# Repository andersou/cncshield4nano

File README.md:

# CNCShield4Nano

Shield para dar suporte CNC ao Arduino Nano com 3-eixos.

## Características
* Possibilidade de prototipação (basicamente 1 camada)
* Aproveitamento de espaço
* Conector separado para alimentação externa do motor

## Board 

![Desenho da placa][placa-img]

## Esquemático

![Esquematico][sch-img]

[placa-img]: img/Board.png
[sch-img]: img/Schematic.png

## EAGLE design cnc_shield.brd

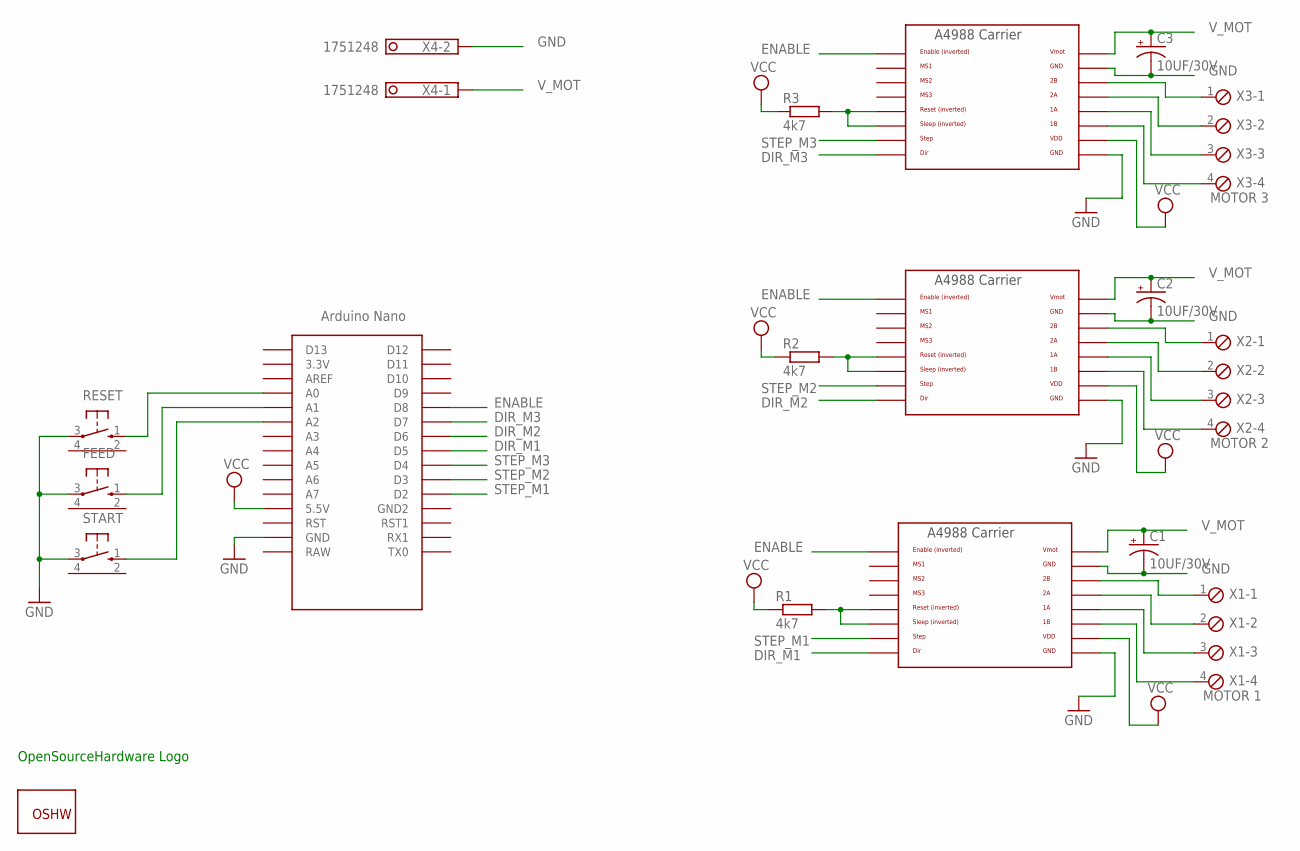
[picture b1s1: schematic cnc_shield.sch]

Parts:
C1, C2, C3: 10UF/30V; E2,5-6
FEED: 10-XX-RPAD; B3F-10XX-RPAD
GOLD_ORB_SM1: OSHWLOGO_GOLD_ORB_SM; OSHW2
R1, R2, R3: 4k7; 0204/5
RESET: 10-XX-RPAD; B3F-10XX-RPAD
START: 10-XX-RPAD; B3F-10XX-RPAD
U$1: NANO
U$2, U$3, U$4: A4988BREAKOUT
X1: MOTOR 1; 4POL254
X2: MOTOR 2; 4POL254
X3: MOTOR 3; 4POL254
X4: 1751248

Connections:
DIR_M1: U$1.D5, U$4.DIR
DIR_M2: U$1.D6, U$2.DIR
DIR_M3: U$1.D7, U$3.DIR
ENABLE: U$1.D8, U$2.EN, U$3.EN, U$4.EN
GND: C1.-, C2.-, C3.-, FEED.3, RESET.3, START.3, U$1.GND, U$2.GND, U$2.GND@0 (GND), U$3.GND, U$3.GND@0 (GND), U$4.GND, U$4.GND@0 (GND), X4.2
unnamed: U$2.2B, X2.1
unnamed: R1.2, U$4.RST, U$4.SLP (SLEEP)
unnamed: U$4.2B, X1.1
unnamed: U$4.2A, X1.2
unnamed: U$4.1A, X1.3
unnamed: U$2.2A, X2.2
unnamed: U$4.1B, X1.4
unnamed: U$2.1A, X2.3
unnamed: U$2.1B, X2.4
unnamed: R2.2, U$2.RST, U$2.SLP (SLEEP)
unnamed: U$3.2B, X3.1
unnamed: U$3.2A, X3.2
unnamed: U$3.1A, X3.3
unnamed: U$3.1B, X3.4
unnamed: R3.2, U$3.RST, U$3.SLP (SLEEP)
unnamed: RESET.1 (S), U$1.A0
unnamed: FEED.1 (S), U$1.A1
unnamed: START.1 (S), U$1.A2
STEP_M1: U$1.D2, U$4.STEP
STEP_M2: U$1.D3, U$2.STEP
STEP_M3: U$1.D4, U$3.STEP
VCC: R1.1, R2.1, R3.1, U$1.5V (5.5V), U$2.VDD, U$3.VDD, U$4.VDD
V_MOT: C1.+, C2.+, C3.+, U$2.VMOT, U$3.VMOT, U$4.VMOT, X4.1

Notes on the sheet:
OpenSourceHardware Logo

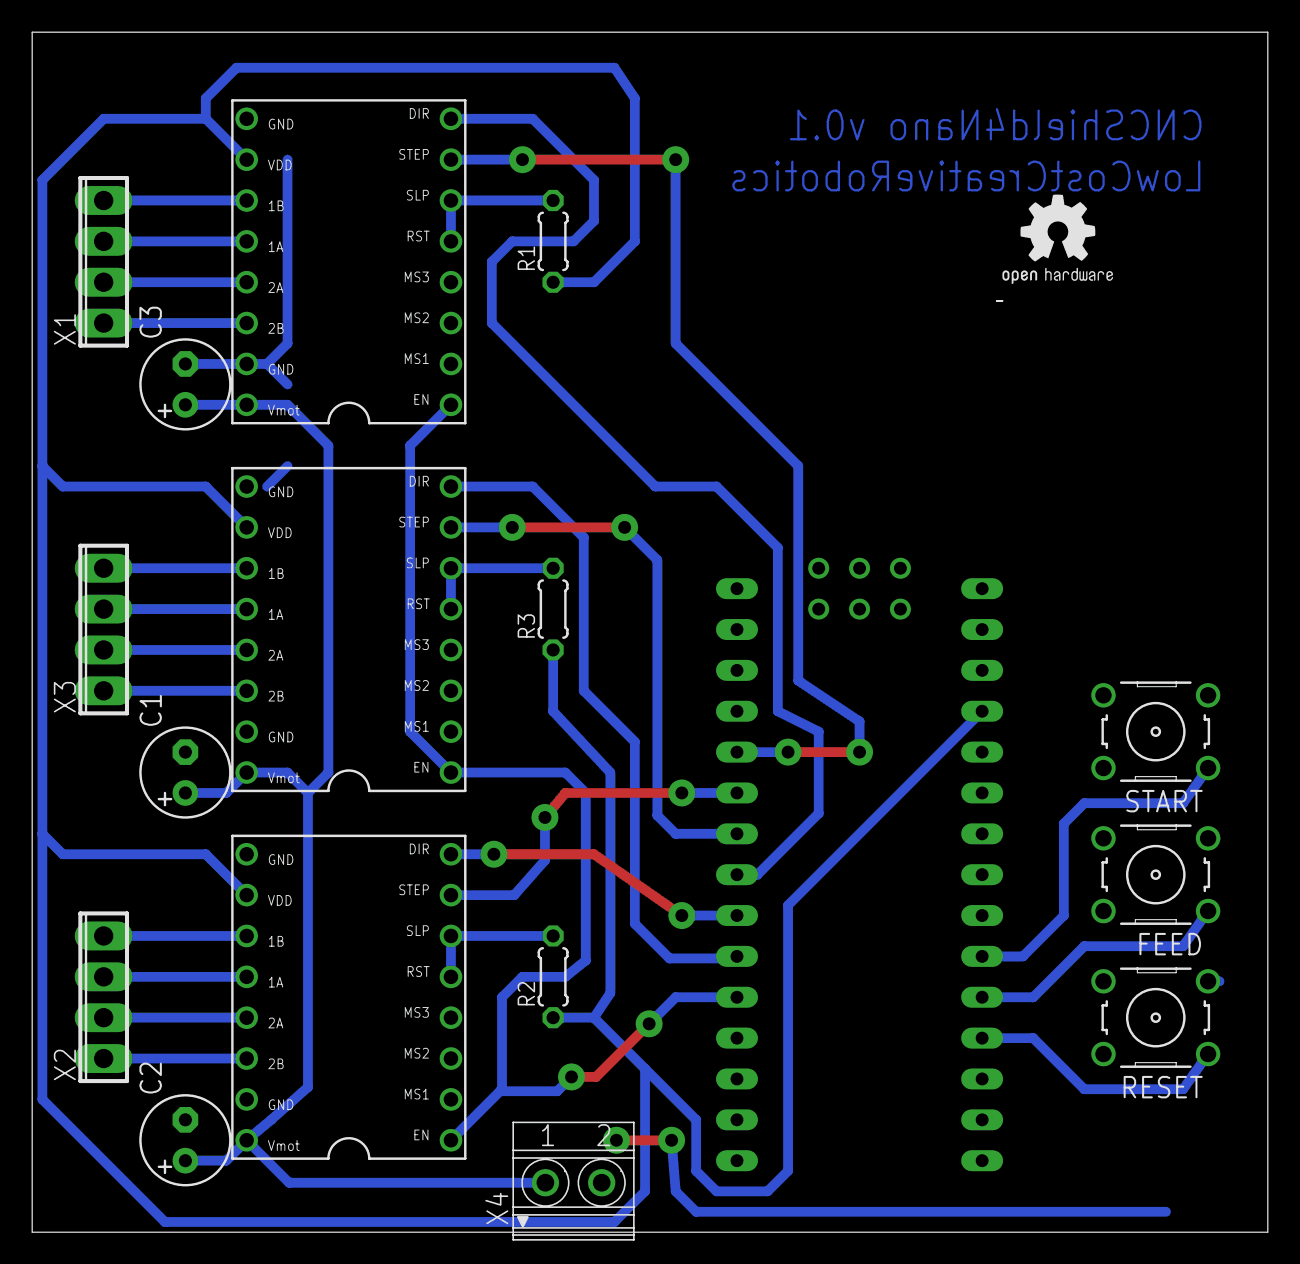
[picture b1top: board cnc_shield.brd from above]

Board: 2 copper layers, 76.8 x 74.6 mm, 18 parts (0 on the bottom side), 28 nets.

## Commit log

2018-08-16 primeira versao
2018-08-16 botoes de entrada
2018-08-16 alimentaçao
2018-08-16 1 versao board
2018-08-20 primeira versao completa da board
